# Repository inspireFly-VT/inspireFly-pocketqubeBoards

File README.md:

# inspireFly-pocketqubeBoards
Multiple boards meant for  use on inspireFly's bus desgin for a pocketqube.

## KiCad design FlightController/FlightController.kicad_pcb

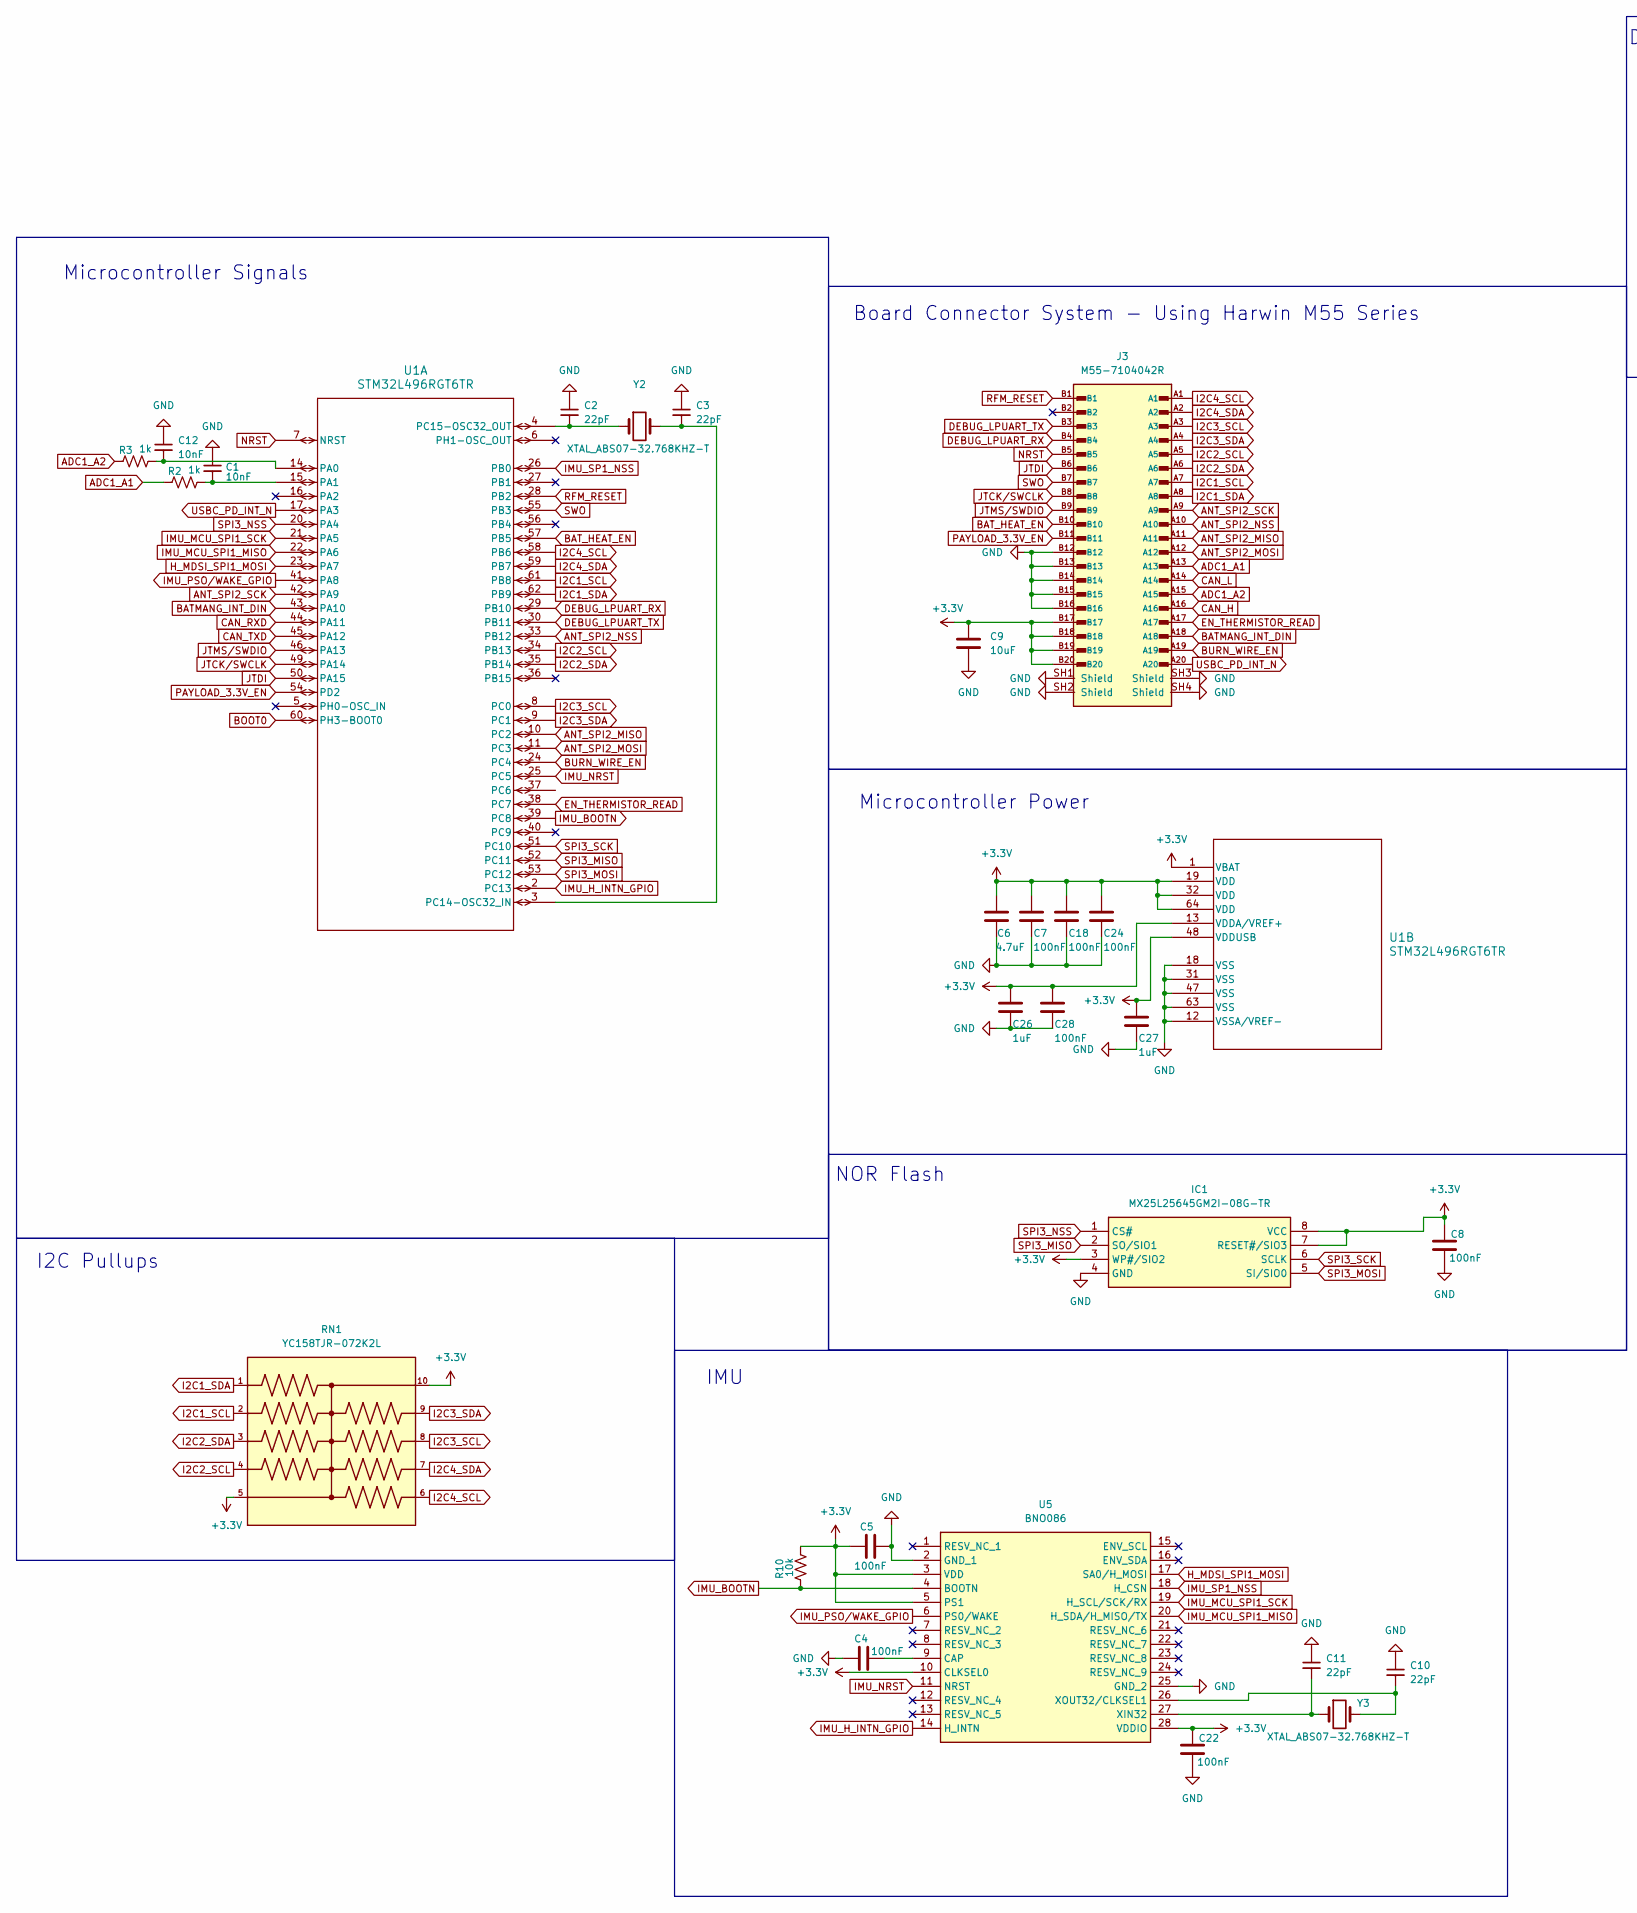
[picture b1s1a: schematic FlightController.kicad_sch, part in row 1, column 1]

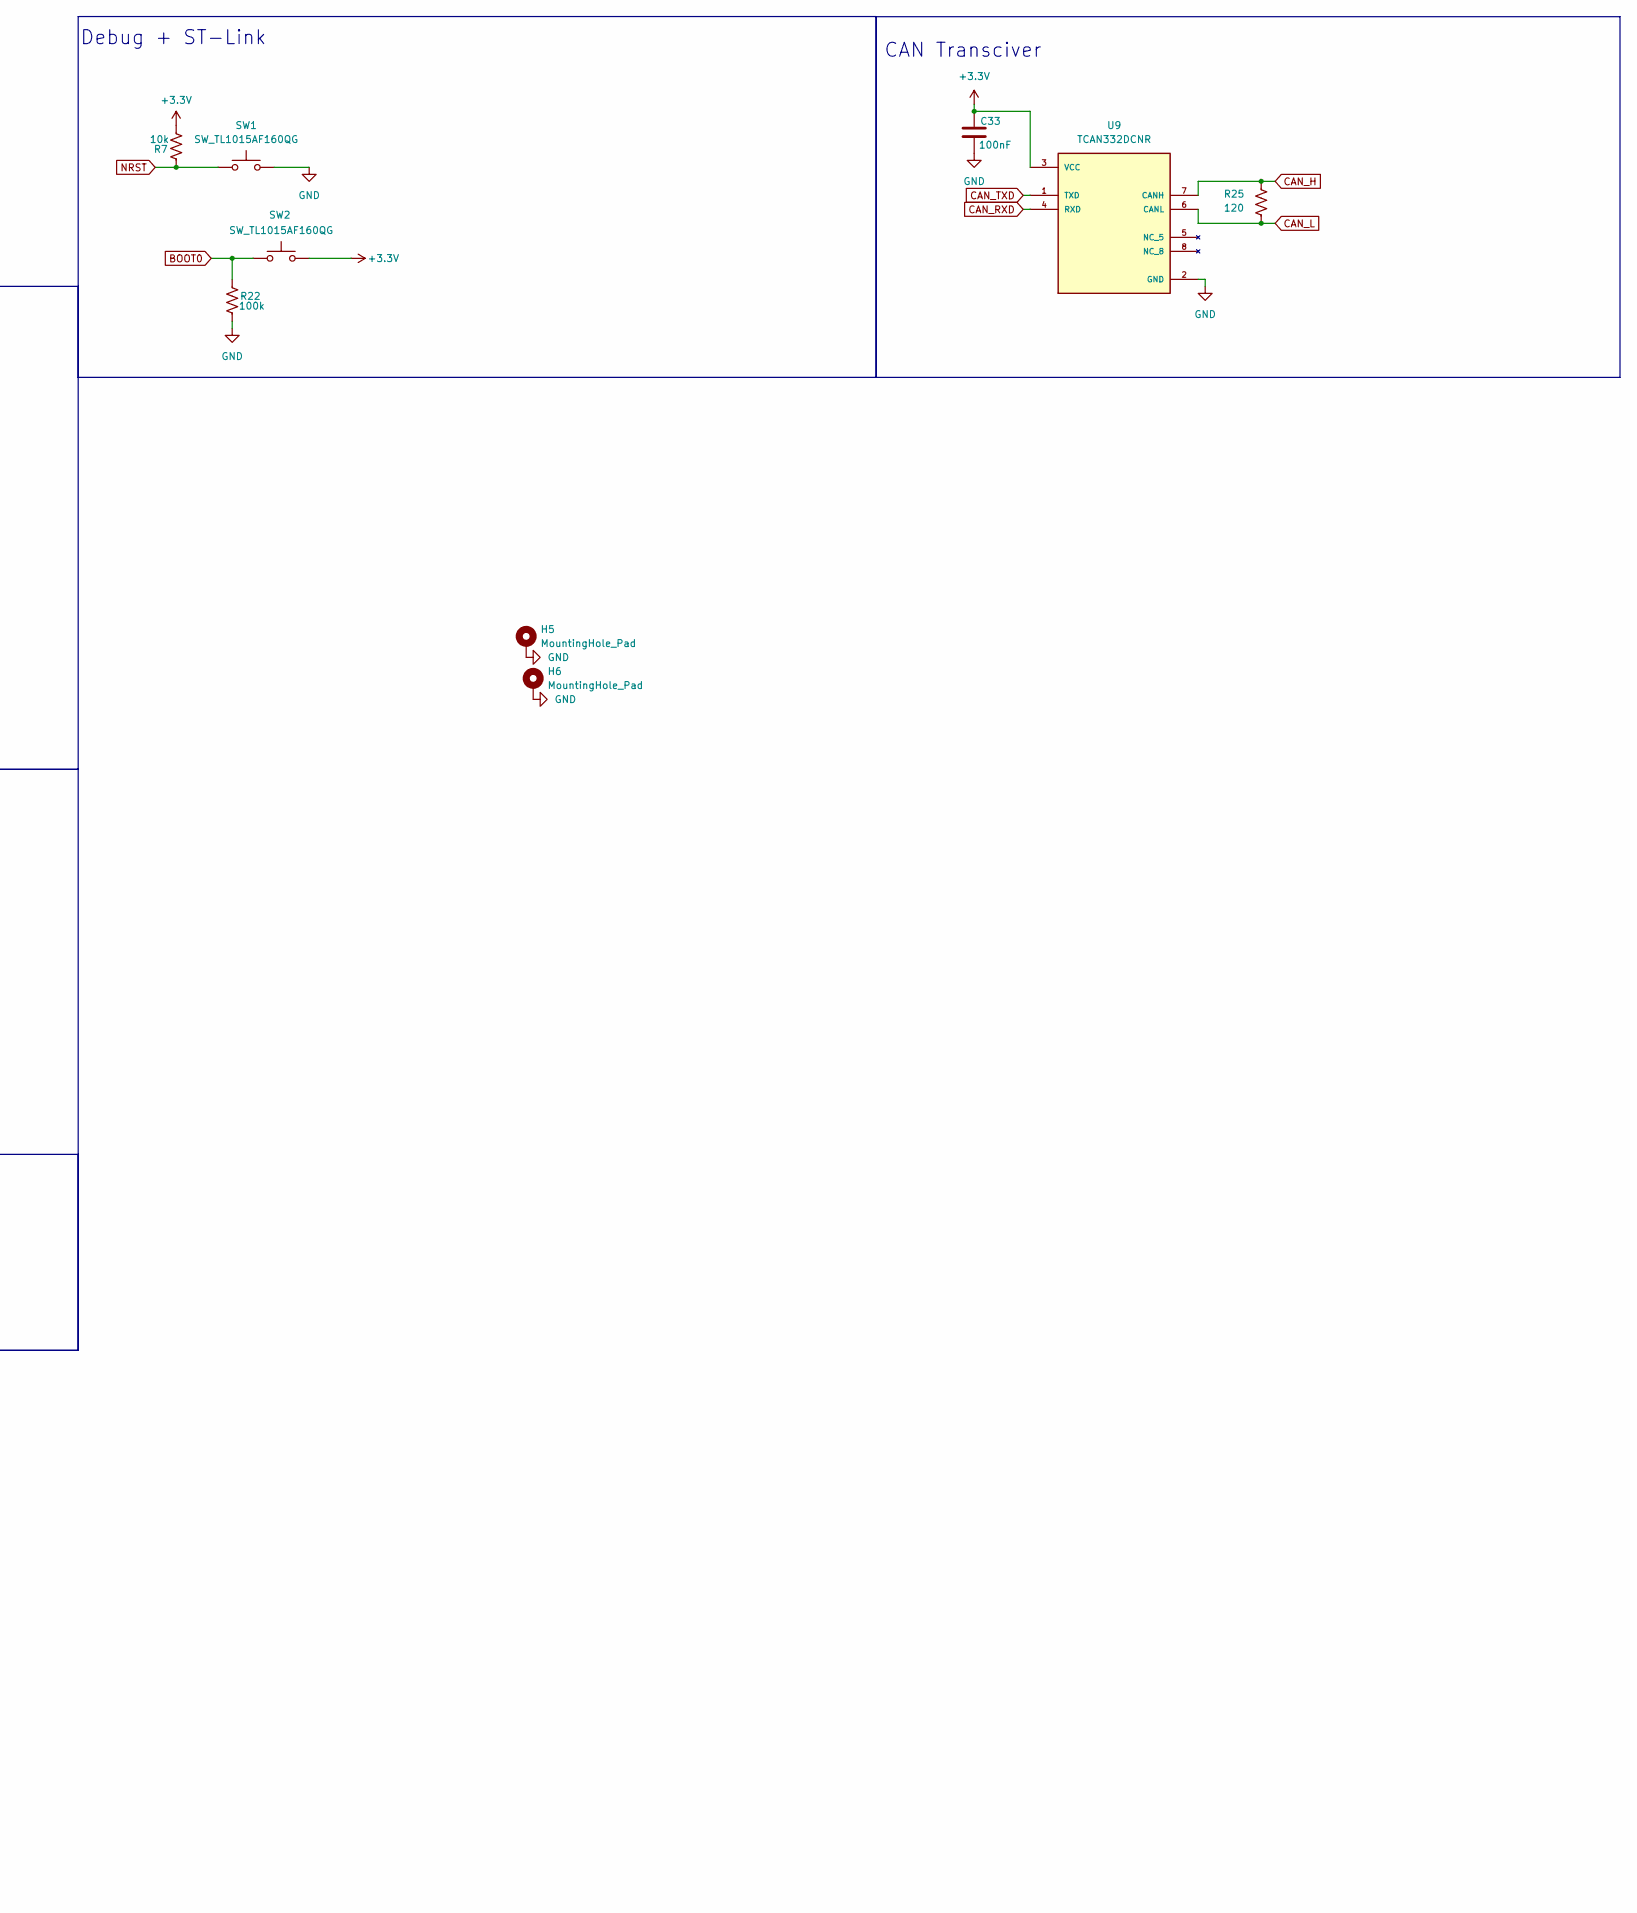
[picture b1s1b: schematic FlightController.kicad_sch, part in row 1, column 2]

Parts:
C1, C12: 10nF; C_0402_1005Metric_Pad0.74x0.62mm_HandSolder
C2, C3, C10, C11: 22pF; C_0402_1005Metric_Pad0.74x0.62mm_HandSolder
C4, C5, C7, C8, C18, C22, C24, C28, C33: 100nF; C_0402_1005Metric_Pad0.74x0.62mm_HandSolder
C6: 4.7uF; C_0603_1608Metric
C9: 10uF; C_0603_1608Metric
C26, C27: 1uF; C_0402_1005Metric_Pad0.74x0.62mm_HandSolder
H5, H6: MountingHole_Pad; MountingHole_2mm_custom
IC1: MX25L25645GM2I-08G-TR; SOIC-8_5.3x5.3mm_P1.27mm; Mouser Part Number 95-25L25645GM2I0TR
J3: M55-7104042R; HARWIN_M55-7104042R
R2, R3: 1k; R_0402_1005Metric_Pad0.72x0.64mm_HandSolder
R7, R10: 10k; R_0402_1005Metric_Pad0.72x0.64mm_HandSolder
R22: 100k; R_0402_1005Metric_Pad0.72x0.64mm_HandSolder
R25: 120; R_0402_1005Metric_Pad0.72x0.64mm_HandSolder
RN1: YC158TJR-072K2L; RESCAXE64P320X160X70-10N
SW1, SW2: SW_TL1015AF160QG
U1: STM32L496RGT6TR; LQFP-64_10x10mm_P0.5mm
U5: BNO086; Mouser Part Number 526-BNO086
U9: TCAN332DCNR; SOT65P280X145-8N; PARTREV E
Y2, Y3: XTAL_ABS07-32.768KHZ-T

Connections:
+3.3V: C5.2, C6.1, C7.1, C8.1, C9.1, C18.1, C22.1, C24.1, C26.1, C27.1, C28.1, C33.1, IC1.3 (WP#/SIO2), IC1.7 (RESET#/SIO3), IC1.8 (VCC), J3.B17, J3.B18, J3.B19, J3.B20, R7.1, R10.1, RN1.5, RN1.10, SW2.2, U1.1 (VBAT), U1.13 (VDDA/VREF+), U1.19 (VDD), U1.32 (VDD), U1.48 (VDDUSB), U1.64 (VDD), U5.3 (VDD), U5.5 (PS1), U5.10 (CLKSEL0), U5.28 (VDDIO), U9.3 (VCC)
ADC1_A1: J3.A13, R2.1
ADC1_A2: J3.A15, R3.1
ANT_SPI2_MISO: J3.A11, U1.10 (PC2)
ANT_SPI2_MOSI: J3.A12, U1.11 (PC3)
ANT_SPI2_NSS: J3.A10, U1.33 (PB12)
ANT_SPI2_SCK: J3.A9, U1.42 (PA9)
BATMANG_INT_DIN: J3.A18, U1.43 (PA10)
BAT_HEAT_EN: J3.B10, U1.57 (PB5)
BOOT0: R22.2, SW2.1, U1.60 (PH3-BOOT0)
BURN_WIRE_EN: J3.A19, U1.24 (PC4)
CAN_H: J3.A16, R25.2, U9.7 (CANH)
CAN_L: J3.A14, R25.1, U9.6 (CANL)
CAN_RXD: U1.44 (PA11), U9.4 (RXD)
CAN_TXD: U1.45 (PA12), U9.1 (TXD)
DEBUG_LPUART_RX: J3.B4, U1.29 (PB10)
DEBUG_LPUART_TX: J3.B3, U1.30 (PB11)
EN_THERMISTOR_READ: J3.A17, U1.38 (PC7)
GND: C1.1, C2.1, C3.1, C4.2, C5.1, C6.2, C7.2, C8.2, C9.2, C10.1, C11.1, C12.1, C18.2, C22.2, C24.2, C26.2, C27.2, C28.2, C33.2, H5.1 (1_1), H6.1 (1_1), IC1.4 (GND), J3.B12, J3.B13, J3.B14, J3.B15, J3.B16, J3.SH1 (Shield), J3.SH2 (Shield), J3.SH3 (Shield), J3.SH4 (Shield), R22.1, SW1.2, U1.12 (VSSA/VREF-), U1.18 (VSS), U1.31 (VSS), U1.47 (VSS), U1.63 (VSS), U5.2 (GND_1), U5.25 (GND_2), U9.2 (GND)
H_MDSI_SPI1_MOSI: U1.23 (PA7), U5.17 (SA0/H_MOSI)
I2C1_SCL: J3.A7, RN1.2, U1.61 (PB8)
I2C1_SDA: J3.A8, RN1.1, U1.62 (PB9)
I2C2_SCL: J3.A5, RN1.4, U1.34 (PB13)
I2C2_SDA: J3.A6, RN1.3, U1.35 (PB14)
I2C3_SCL: J3.A3, RN1.8, U1.8 (PC0)
I2C3_SDA: J3.A4, RN1.9, U1.9 (PC1)
I2C4_SCL: J3.A1, RN1.6, U1.58 (PB6)
I2C4_SDA: J3.A2, RN1.7, U1.59 (PB7)
IMU_BOOTN: R10.2, U1.39 (PC8), U5.4 (BOOTN)
IMU_H_INTN_GPIO: U1.2 (PC13), U5.14 (H_INTN)
IMU_MCU_SPI1_MISO: U1.22 (PA6), U5.20 (H_SDA/H_MISO/TX)
IMU_MCU_SPI1_SCK: U1.21 (PA5), U5.19 (H_SCL/SCK/RX)
IMU_NRST: U1.25 (PC5), U5.11 (NRST)
IMU_PSO/WAKE_GPIO: U1.41 (PA8), U5.6 (PS0/WAKE)
IMU_SP1_NSS: U1.26 (PB0), U5.18 (H_CSN)
JTCK/SWCLK: J3.B8, U1.49 (PA14)
JTDI: J3.B6, U1.50 (PA15)
JTMS/SWDIO: J3.B9, U1.46 (PA13)
NRST: J3.B5, R7.2, SW1.1, U1.7 (NRST)
unnamed: C12.2, R3.2, U1.14 (PA0)
unnamed: C1.2, R2.2, U1.15 (PA1)
unnamed: C3.2, U1.3 (PC14-OSC32_IN), Y2.2
unnamed: C2.2, U1.4 (PC15-OSC32_OUT), Y2.1
unnamed: C4.1, U5.9 (CAP)
unnamed: C11.2, U5.27 (XIN32), Y3.1
unnamed: C10.2, U5.26 (XOUT32/CLKSEL1), Y3.2
PAYLOAD_3.3V_EN: J3.B11, U1.54 (PD2)
RFM_RESET: J3.B1, U1.28 (PB2)
SPI3_MISO: IC1.2 (SO/SIO1), U1.52 (PC11)
SPI3_MOSI: IC1.5 (SI/SIO0), U1.53 (PC12)
SPI3_NSS: IC1.1 (CS#), U1.20 (PA4)
SPI3_SCK: IC1.6 (SCLK), U1.51 (PC10)
SWO: J3.B7, U1.55 (PB3)
USBC_PD_INT_N: J3.A20, U1.17 (PA3)

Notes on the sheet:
Board Connector System - Using Harwin M55 Series
CAN Transciver
Microcontroller Signals
NOR Flash
Debug + ST-Link
I2C Pullups
Microcontroller Power
IMU

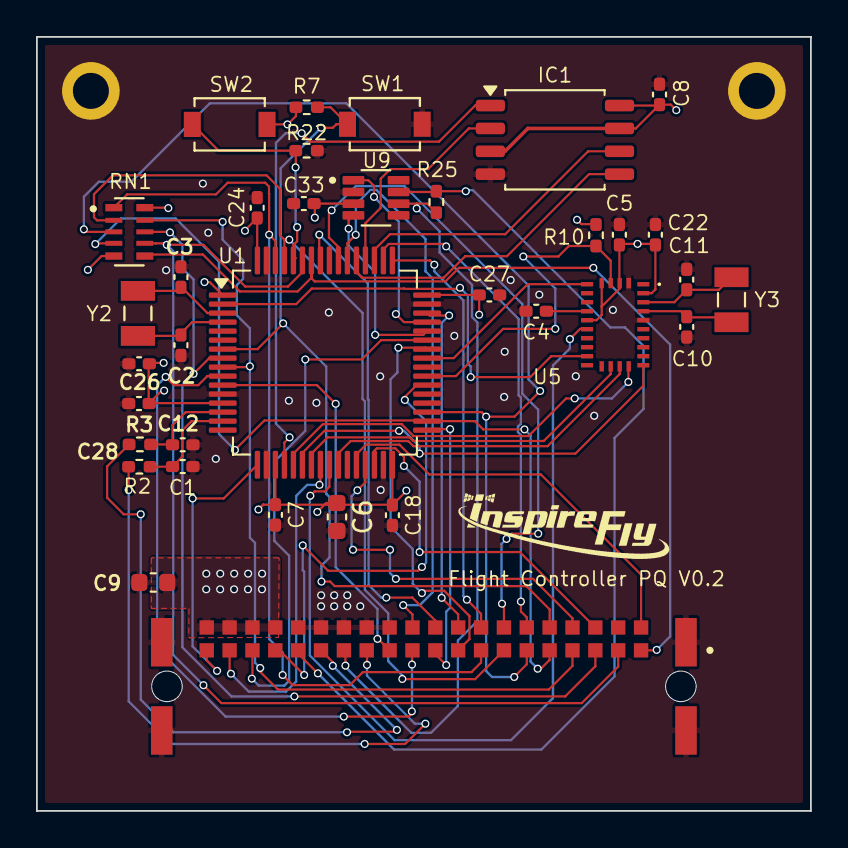
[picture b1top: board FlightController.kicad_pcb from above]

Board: 4 copper layers, 43.0 x 43.0 mm, 37 parts (0 on the bottom side), 54 nets.

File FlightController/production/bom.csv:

Designator,Footprint,Quantity,Value,LCSC Part #
"C1, C12",0402,2,10nF,
"C10, C11, C2, C3",0402,4,22pF,
"C18, C22, C24, C28, C33, C4, C5, C7, C8",0402,9,100nF,
"C26, C27",0402,2,1uF,
C6,0603,1,4.7uF,
C9,0603,1,10uF,
IC1,SOIC-8_5.3x5.3mm_P1.27mm,1,MX25L25645GM2I-08G-TR,
J3,HARWIN_M55-7104042R,1,M55-7104042R,
J5,PinHeader_1x02_P2.54mm_Vertical,1,Conn_01x02_Pin,
"R10, R7",0402,2,10k,
"R2, R3",0402,2,1k,
R22,0402,1,100k,
R25,0402,1,120,
RN1,RESCAXE64P320X160X70-10N,1,YC158TJR-072K2L,
"SW1, SW2",SW_TL1015AF160QG,2,SW_TL1015AF160QG,
U1,LQFP-64_10x10mm_P0.5mm,1,STM32L496RGT6TR,
U5,BNO086,1,BNO086,
U9,SOT65P280X145-8N,1,TCAN332DCNR,
"Y2, Y3",XTAL_ABS07-32.768KHZ-T,2,XTAL_ABS07-32.768KHZ-T,

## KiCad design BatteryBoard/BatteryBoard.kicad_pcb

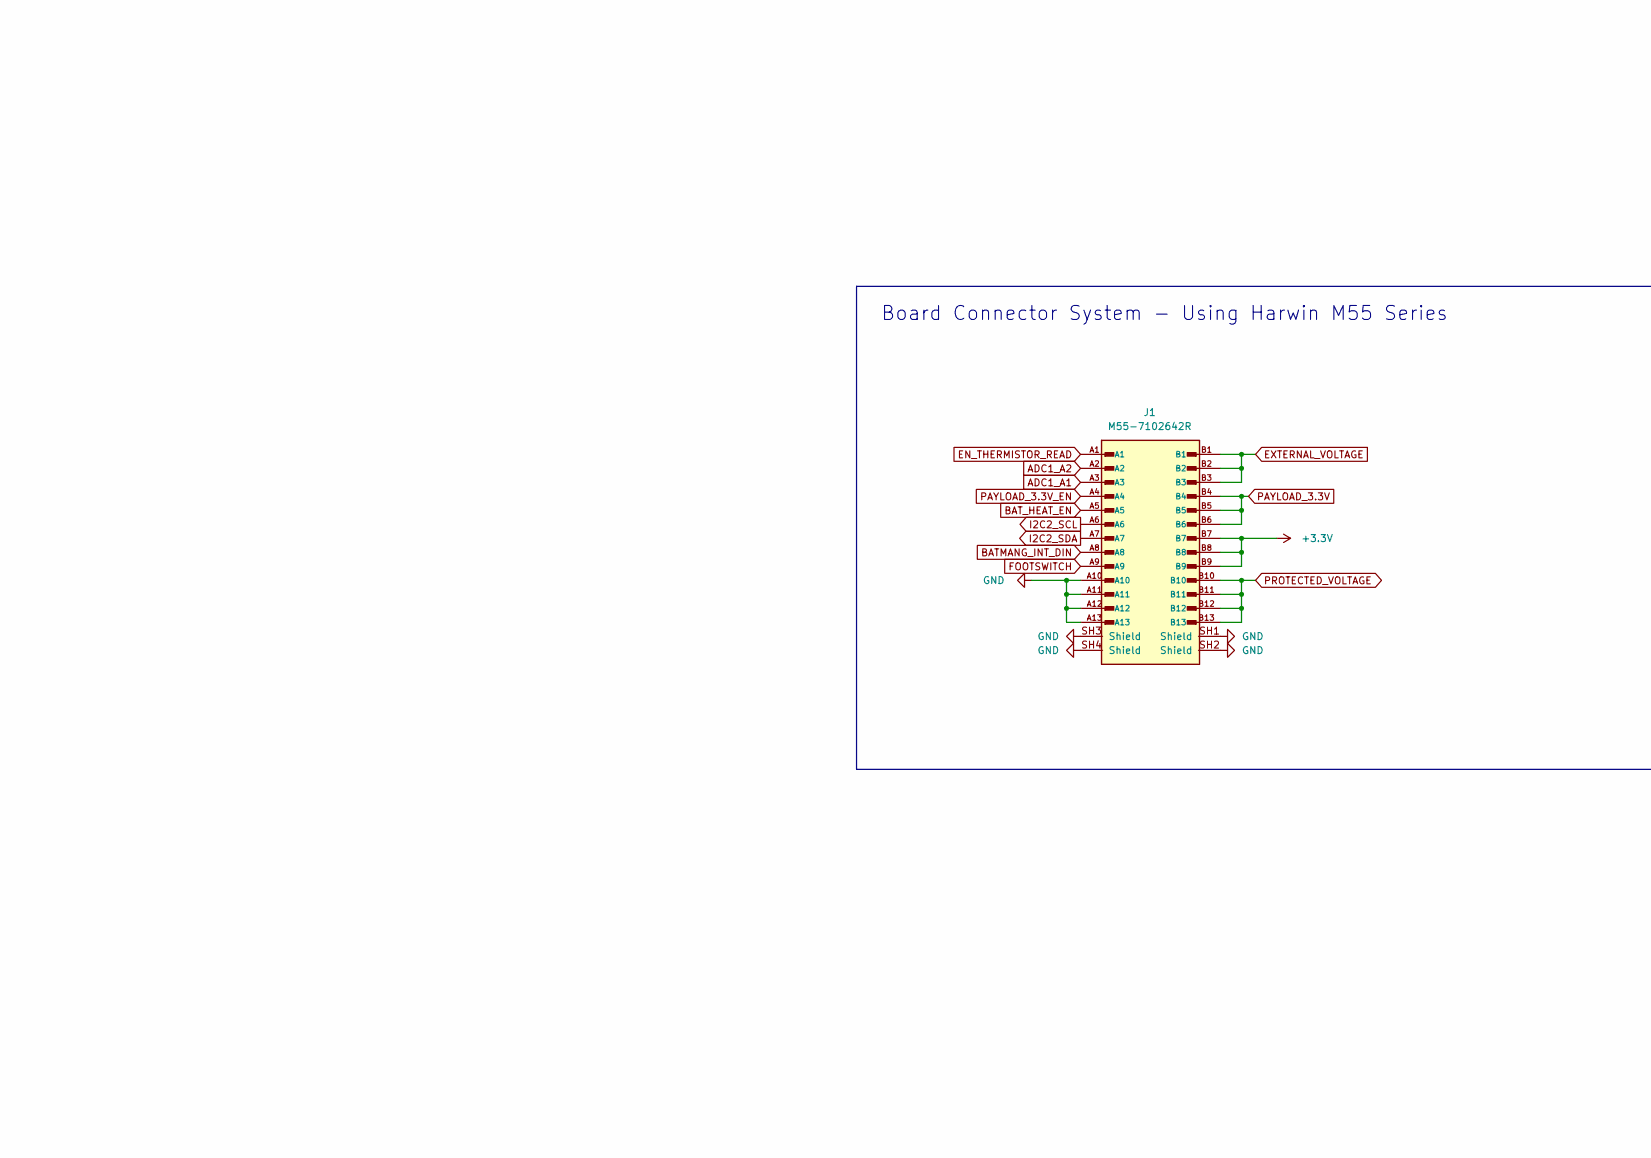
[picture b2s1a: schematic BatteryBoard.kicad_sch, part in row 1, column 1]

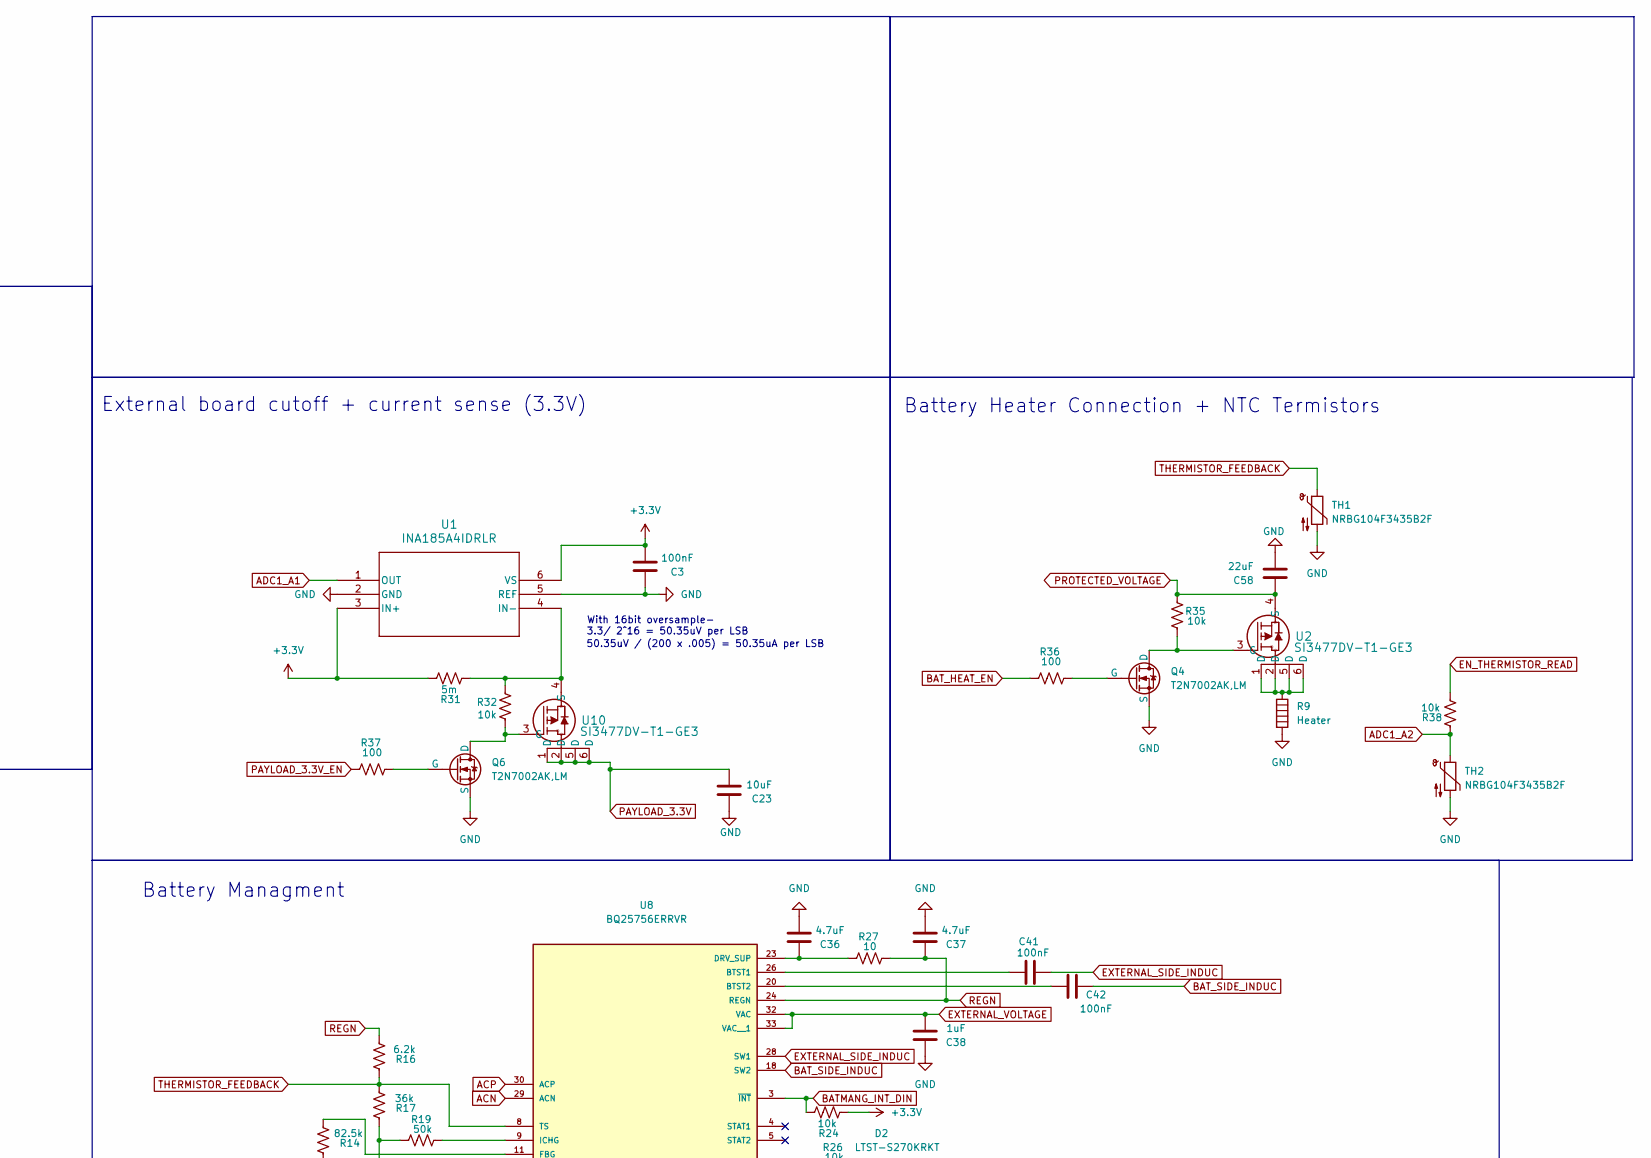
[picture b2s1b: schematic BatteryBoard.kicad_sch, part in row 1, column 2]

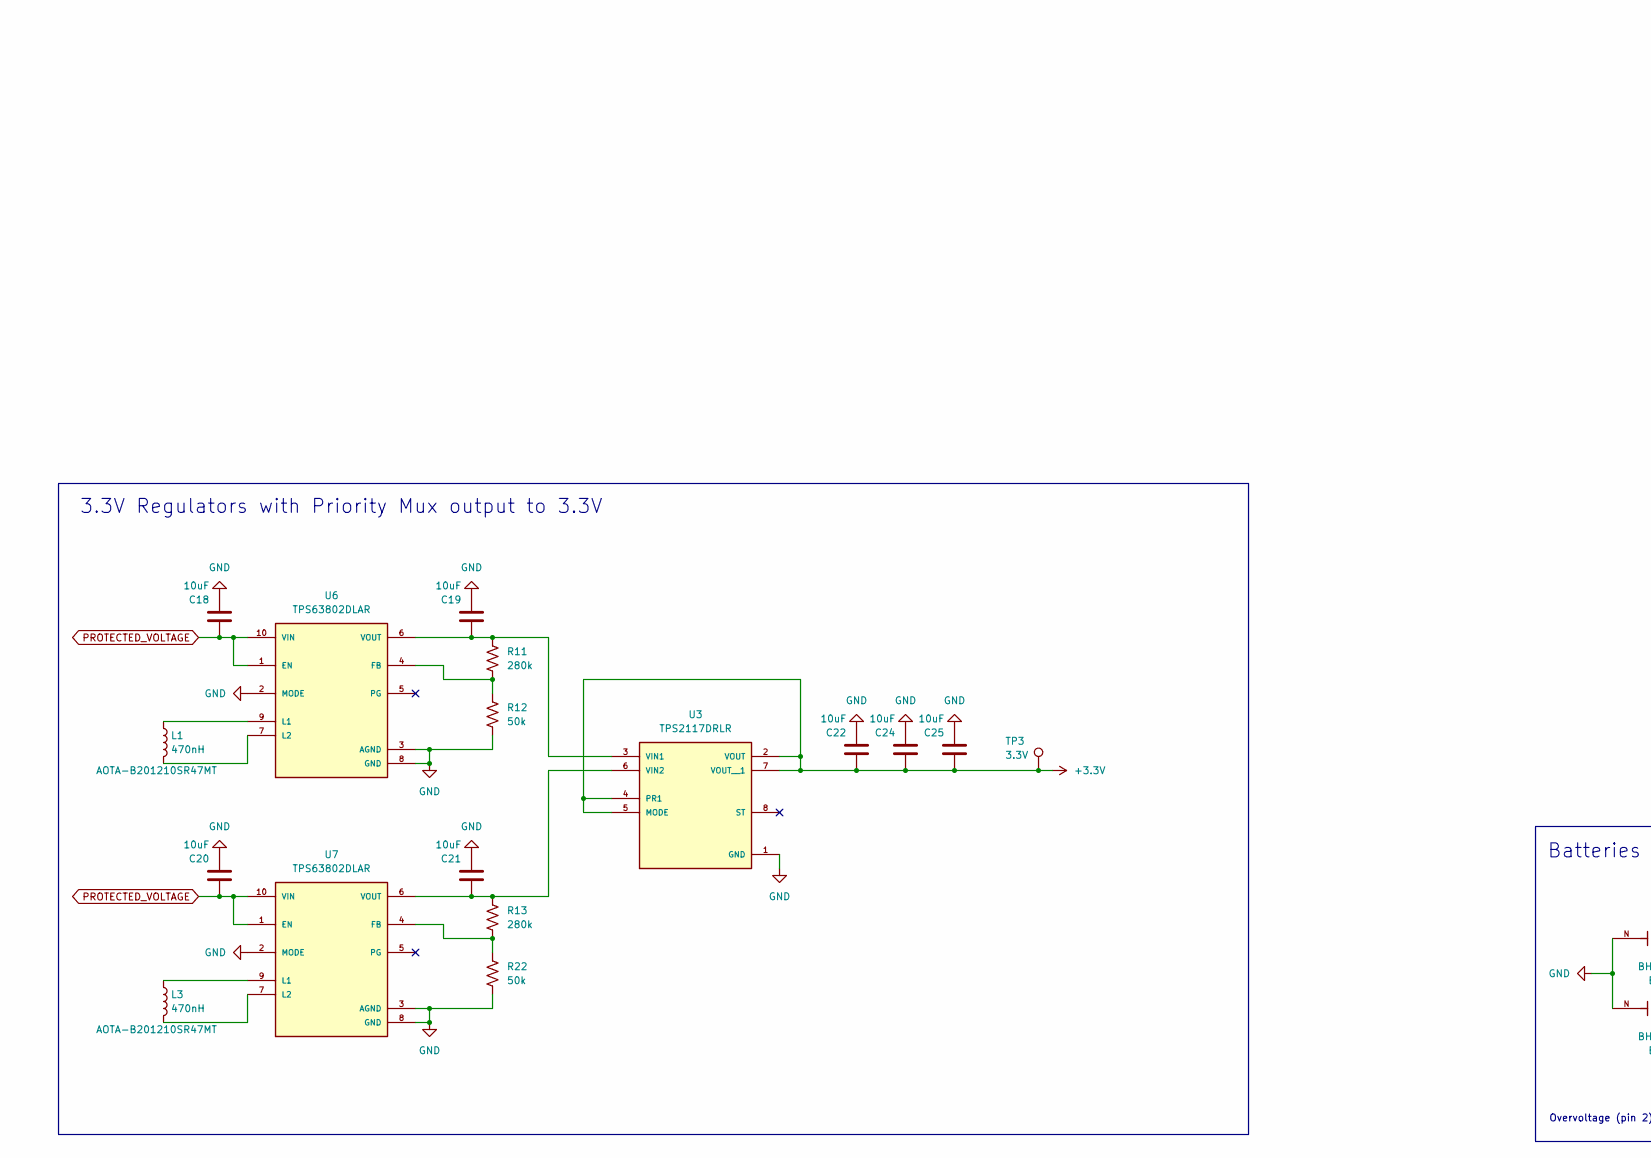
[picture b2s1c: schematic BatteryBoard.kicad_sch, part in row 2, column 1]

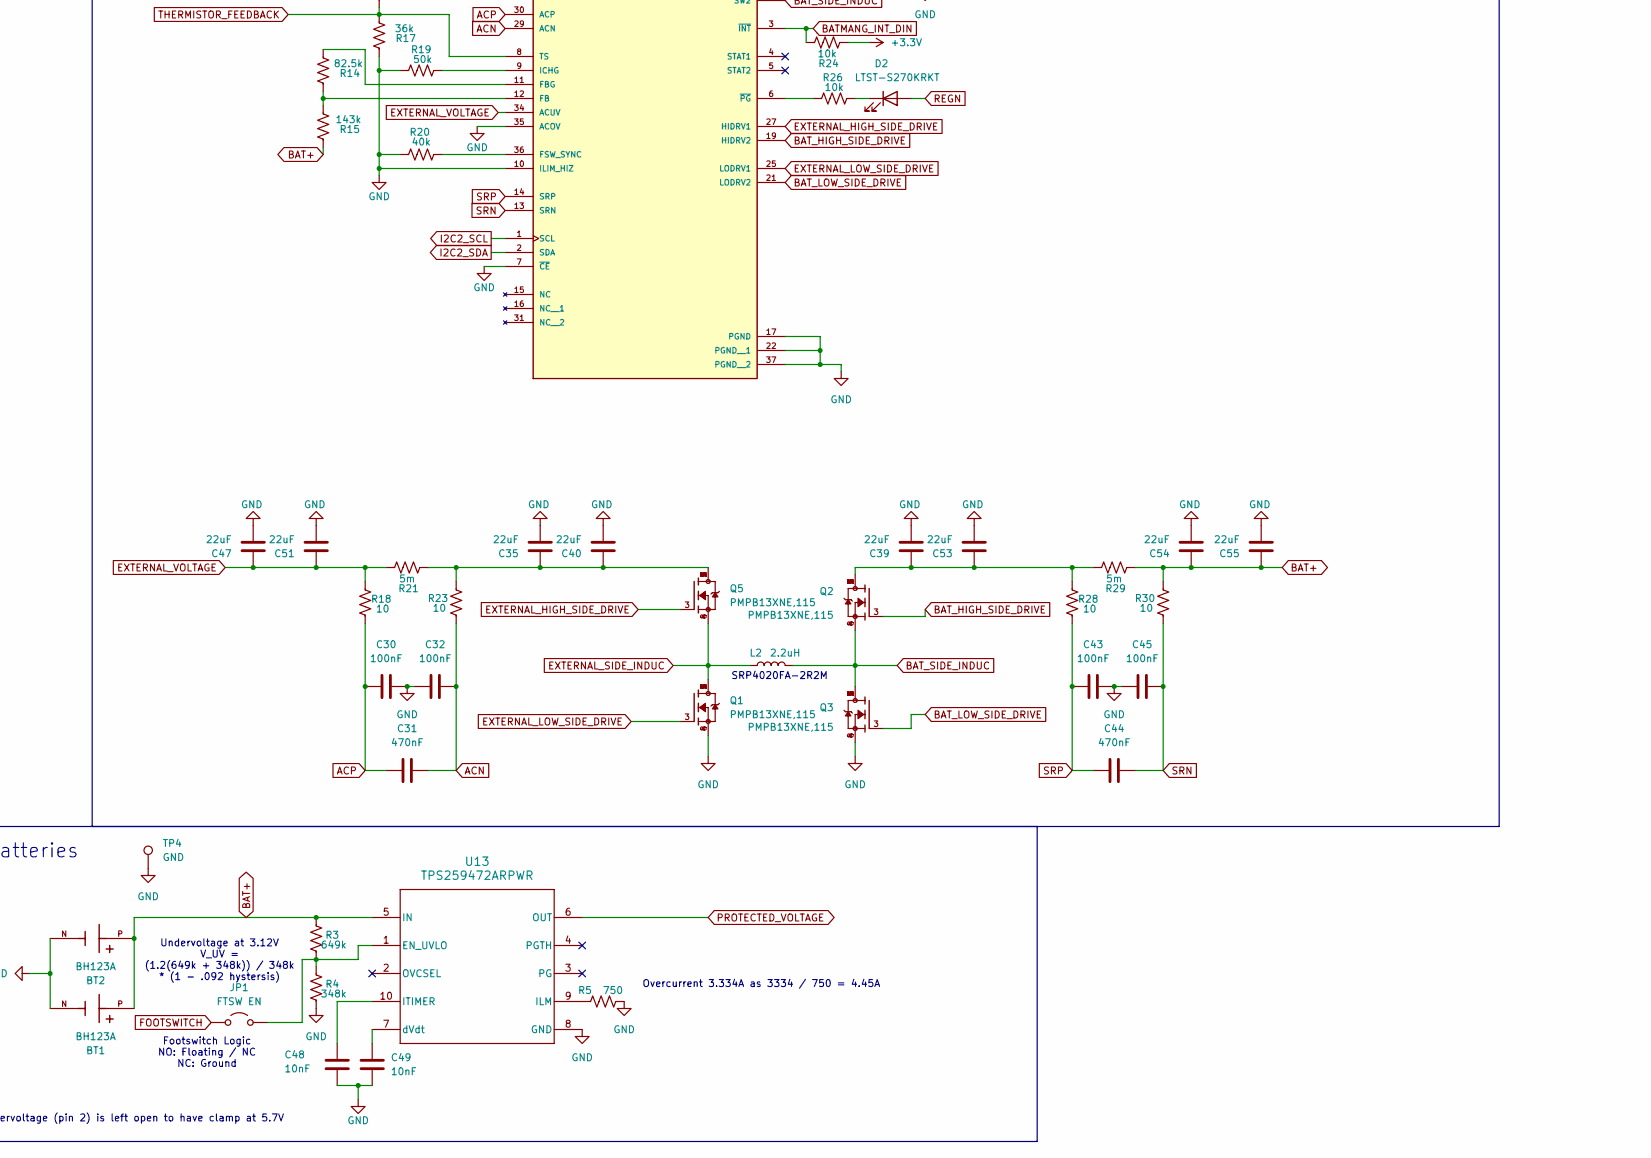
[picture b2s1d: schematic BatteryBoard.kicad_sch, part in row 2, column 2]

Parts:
BT1, BT2: BH123A; BAT_BH123A; PARTREV E
C3, C30, C32, C41, C42, C43, C45: 100nF; C_0402_1005Metric_Pad0.74x0.62mm_HandSolder
C18, C19, C20, C21, C22, C23, C24, C25: 10uF; C_0603_1608Metric
C31, C44: 470nF; C_0402_1005Metric_Pad0.74x0.62mm_HandSolder
C35, C39, C40, C47, C51, C53, C54, C55, C58: 22uF; C_1210_3225Metric
C36, C37: 4.7uF; C_0603_1608Metric
C38: 1uF; C_0402_1005Metric_Pad0.74x0.62mm_HandSolder
C48, C49: 10nF; C_0402_1005Metric_Pad0.74x0.62mm_HandSolder
D2: LTST-S270KRKT; LED_0603_1608Metric_Pad1.05x0.95mm_HandSolder
J1: M55-7102642R; HARWIN_M55-7102642R
JP1: FTSW EN; SmallJumper
L1, L3: 470nH; L_0805_2012Metric_Pad1.05x1.20mm_HandSolder
L2: 2.2uH; IND_SRP4020FA-2R2M_BRN
Q1, Q2, Q3, Q5: PMPB13XNE,115; TRANS_PMPB11EN_115
Q4, Q6: T2N7002AK,LM; SOT-23-3
R3: 649k; R_0402_1005Metric
R4: 348k; R_0402_1005Metric
R5: 750; R_0402_1005Metric_Pad0.72x0.64mm_HandSolder
R9: Heater; HeaterConnection
R11, R13: 280k; R_0402_1005Metric_Pad0.72x0.64mm_HandSolder
R12, R19, R22: 50k; R_0402_1005Metric_Pad0.72x0.64mm_HandSolder
R14: 82.5k; R_0402_1005Metric_Pad0.72x0.64mm_HandSolder
R15: 143k; R_0402_1005Metric_Pad0.72x0.64mm_HandSolder
R16: 6.2k; R_0402_1005Metric_Pad0.72x0.64mm_HandSolder
R17: 36k; R_0402_1005Metric_Pad0.72x0.64mm_HandSolder
R18, R23, R27, R28, R30: 10; R_0402_1005Metric_Pad0.72x0.64mm_HandSolder
R20: 40k; R_0402_1005Metric_Pad0.72x0.64mm_HandSolder
R21, R29, R31: 5m; R_1206_3216Metric_Pad1.30x1.75mm_HandSolder
R24, R26, R32, R35, R38: 10k; R_0402_1005Metric_Pad0.72x0.64mm_HandSolder
R36, R37: 100; R_0402_1005Metric_Pad0.72x0.64mm_HandSolder
TH1, TH2: NRBG104F3435B2F
TP3: 3.3V; TestPoint_Pad_D1.0mm
TP4: GND; TestPoint_Pad_D1.0mm
U1: INA185A4IDRLR; SOT_INA185_TEX
U2, U10: SI3477DV-T1-GE3; SOT_V-T1-GE3_VIS-M
U3: TPS2117DRLR; SOTFL50P160X60-8N; PARTREV A
U6, U7: TPS63802DLAR; VREG_TPS63802DLAR; PARTREV B
U8: BQ25756ERRVR; IC_BQ25756ERRVR; PARTREV November 2023
U13: TPS259472ARPWR; RPW0010A-MFG

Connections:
+3.3V: C3.2, C22.1, C24.1, C25.1, J1.B7, J1.B8, J1.B9, R24.2, R31.1, TP3.1 (1_1), U1.3 (IN+), U1.6 (VS), U3.2 (VOUT), U3.4 (PR1), U3.5 (MODE), U3.7 (VOUT__1)
ACN: C31.2, C32.2, R23.1, U8.29 (ACN)
ACP: C30.1, C31.1, R18.1, U8.30 (ACP)
ADC1_A1: J1.A3, U1.1 (OUT)
ADC1_A2: J1.A2, R38.2, TH2.1
BAT+: BT1.P, BT2.P, C54.1, C55.1, R3.2, R15.2, R29.2, R30.2, U13.5 (IN)
BATMANG_INT_DIN: J1.A8, R24.1, U8.3 (~INT)
BAT_HEAT_EN: J1.A5, R36.2
BAT_HIGH_SIDE_DRIVE: Q2.3, U8.19 (HIDRV2)
BAT_LOW_SIDE_DRIVE: Q3.3, U8.21 (LODRV2)
BAT_SIDE_INDUC: C42.1, L2.2, Q2.4, Q2.8, Q3.1, Q3.2, Q3.5, Q3.6, Q3.7, U8.18 (SW2)
EN_THERMISTOR_READ: J1.A1, R38.1
EXTERNAL_HIGH_SIDE_DRIVE: Q5.3, U8.27 (HIDRV1)
EXTERNAL_LOW_SIDE_DRIVE: Q1.3, U8.25 (LODRV1)
EXTERNAL_SIDE_INDUC: C41.1, L2.1, Q1.1, Q1.2, Q1.5, Q1.6, Q1.7, Q5.4, Q5.8, U8.28 (SW1)
EXTERNAL_VOLTAGE: C38.2, C47.1, C51.1, J1.B1, J1.B2, J1.B3, R18.2, R21.1, U8.32 (VAC), U8.33 (VAC__1), U8.34 (ACUV)
FOOTSWITCH: J1.A9, JP1.1 (A)
GND: BT1.N, BT2.N, C3.1, C18.2, C19.2, C20.2, C21.2, C22.2, C23.1, C24.2, C25.2, C30.2, C32.1, C35.2, C36.2, C37.2, C38.1, C39.2, C40.2, C43.2, C45.1, C47.2, C48.1, C49.1, C51.2, C53.2, C54.2, C55.2, C58.2, J1.A10, J1.A11, J1.A12, J1.A13, J1.SH1 (Shield), J1.SH2 (Shield), J1.SH3 (Shield), J1.SH4 (Shield), Q1.4, Q1.8, Q3.4, Q3.8, Q4.3 (S), Q6.3 (S), R4.1, R5.1, R9.2, R12.2, R17.2, R19.2, R20.1, R22.2, TH1.2, TH2.2, TP4.1 (1_1), U1.2 (GND), U1.5 (REF), U3.1 (GND), U6.2 (MODE), U6.3 (AGND), U6.8 (GND), U7.2 (MODE), U7.3 (AGND), U7.8 (GND), U8.7 (~CE), U8.10 (ILIM_HIZ), U8.17 (PGND), U8.22 (PGND__1), U8.35 (ACOV), U8.37 (PGND__2), U13.8 (GND)
I2C2_SCL: J1.A6, U8.1 (SCL)
I2C2_SDA: J1.A7, U8.2 (SDA)
unnamed: C35.1, C40.1, Q5.1, Q5.2, Q5.5, Q5.6, Q5.7, R21.2, R23.2
unnamed: C39.1, C53.1, Q2.1, Q2.2, Q2.5, Q2.6, Q2.7, R28.2, R29.1
unnamed: D2.1 (K), R26.1
unnamed: JP1.2 (B), R3.1, R4.2, U13.1 (EN_UVLO)
unnamed: Q4.1 (D), R35.1, U2.3 (G)
unnamed: Q4.2 (G), R36.1
unnamed: Q6.1 (D), R32.2, U10.3 (G)
unnamed: Q6.2 (G), R37.1
unnamed: R9.1, U2.1 (D), U2.2 (D), U2.5 (D), U2.6 (D)
unnamed: R31.2, R32.1, U1.4 (IN-), U10.4 (S)
unnamed: C19.1, R11.1, U3.3 (VIN1), U6.6 (VOUT)
unnamed: C21.1, R13.1, U3.6 (VIN2), U7.6 (VOUT)
unnamed: R11.2, R12.1, U6.4 (FB)
unnamed: L1.1, U6.9 (L1)
unnamed: L1.2, U6.7 (L2)
unnamed: R13.2, R22.1, U7.4 (FB)
unnamed: L3.1, U7.9 (L1)
unnamed: L3.2, U7.7 (L2)
unnamed: C41.2, U8.26 (BTST1)
unnamed: C42.2, U8.20 (BTST2)
unnamed: C36.1, R27.1, U8.23 (DRV_SUP)
unnamed: R14.2, R15.1, U8.12 (FB)
unnamed: R14.1, U8.11 (FBG)
unnamed: R20.2, U8.36 (FSW_SYNC)
unnamed: R19.1, U8.9 (ICHG)
unnamed: R26.2, U8.6 (~PG)
unnamed: R5.2, U13.9 (ILM)
unnamed: C48.2, U13.10 (ITIMER)
unnamed: C49.2, U13.7 (dVdt)
PAYLOAD_3.3V: C23.2, J1.B4, J1.B5, J1.B6, U10.1 (D), U10.2 (D), U10.5 (D), U10.6 (D)
PAYLOAD_3.3V_EN: J1.A4, R37.2
PROTECTED_VOLTAGE: C18.1, C20.1, C58.1, J1.B10, J1.B11, J1.B12, J1.B13, R35.2, U2.4 (S), U6.1 (EN), U6.10 (VIN), U7.1 (EN), U7.10 (VIN), U13.6 (OUT)
REGN: C37.1, D2.2 (A), R16.1, R27.2, U8.24 (REGN)
SRN: C44.2, C45.2, R30.1, U8.13 (SRN)
SRP: C43.1, C44.1, R28.1, U8.14 (SRP)
THERMISTOR_FEEDBACK: R16.2, R17.1, TH1.1, U8.8 (TS)

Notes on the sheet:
SRP4020FA-2R2M
With 16bit oversample-
Undervoltage at 3.12V V_UV = (1.2(649k + 348k)) / 348k * (1 - .092 hystersis)
Board Connector System - Using Harwin M55 Series
Batteries
Battery Managment
50.35uV / (200 x .005) = 50.35uA per LSB
3.3V Regulators with Priority Mux output to 3.3V
External board cutoff + current sense (3.3V)
3.3/ 2^16 = 50.35uV per LSB
Footswitch Logic NO: Floating / NC NC: Ground
Overvoltage (pin 2) is left open to have clamp at 5.7V
Overcurrent 3.334A as 3334 / 750 = 4.45A
Battery Heater Connection + NTC Termistors
